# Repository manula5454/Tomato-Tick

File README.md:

# TomatoTick 2D Pomodoro Timer PCB only 
A PCB in the shape of a Tomato that runs a pomodoro timer of 30 minutes studying and 5 minutes break on repeat.
Here is the final render of my project!!

## This project is used to have a physical timer for studying that is a physical object instead of a digital site/app. The TomatoTick is meant to exist only as a PCB for a theatrical aspect and easy build process. The microchip is a XIAO RP2350 and powers the main display of an OLED SSD1306 which repeats a 30 minutes timer and 5 minute break when started. 

* Pomodoro Timer
* Quick and Easy digital timer build
* Exam study help

## Using this repo:
1. Code is located in [Arduino](Arduino)
2. Kicad files including libraries, schematics, pcb etc. are located in [PCB](PCB)
3. Gerbers.zip can be used to directly send PCB to vendors.

## heres how I made the project :)
1. Used Kicad and made a simple schematic with my parts (see BOM.csv)
2. Download all the Seeed libraries for the XIAO 2350
3. After the schematic is finished turn into PCB view and simply make a tomato shape on the edge faces layer
4. Add the traces to each component (use the render image above for reference)
5. Change the film colour to add the 'red' tomato

## Code - Arduino IDE
Libraries : 

#include <Wire.h>

#include <Adafruit_GFX.h>

#include <Adafruit_SSD1306.h>

(Can all be found inside the IDE library )

void(displayStudytime) -- Displays remaining study time on OLED screen
void(displayBreaktime) -- Displays remaining study time on OLED

buttonPin -- 1 press = pause, long press = reset {rp.2040 reboot();}

LED functions - builds up (e.g. LED5 lights up, then LED4....)

## Schematic of Tomato-Tick

### Bill of Materials (See BOM.cv)

| Reference | Part | Qty | Description | Vendor | Unit Price | Link |
| :--- | :--- | :---: | :--- | :--- | :---: | :--- |
| U2 | XIAO RP2350 | 1 | Microcontroller module | Seeed Studio | $5.90 | https://seeedstudio.com |
| D0 D1 D2 D3 D6 D7 | LED 3mm | 6 | Countdown LEDs | Core Electronics | $0.60 | https://core-electronics.com.au |
| R0 R1 R2 R3 R6 R7 | 330R resistor | 6 | LED current-limit resistors | Core Electronics | $1.58 | https://core-electronics.com.au |
| R9 | 1k resistor | 1 | Transistor base resistor | N/A | N/A | *Have one at home* |
| Q1 | 2N3904 transistor | 1 | NPN transistor for the buzzer | Core Electronics | $0.30 | https://core-electronics.com.au |
| SW2 | 6mm tactile button | 1 | Pause and reset button | Core Electronics | $0.36 | https://core-electronics.com.au |
| BZ1 | 5V active buzzer | 1 | Alert buzzer | Core Electronics | $0.27 | https://core-electronics.com.au |
| J1 | 1x4 pin header | 1 | OLED connector | Core Electronics | $0.11 | https://core-electronics.com.au |
| U1 | 1x7 pin header | 2 | Microcontroller connector | Core Electronics | $1.26 | https://core-electronics.com.au |
| OLED1 | White I2C OLED display (SSD1306) | 1 | 0.96in display | Core Electronics | $5.05 | https://core-electronics.com.au |
|     |  |                                  |  |               Shipping & GST Cost | $5.99 |  |
|     |  |                                  |  |               Total Cost | $25.63 |  |

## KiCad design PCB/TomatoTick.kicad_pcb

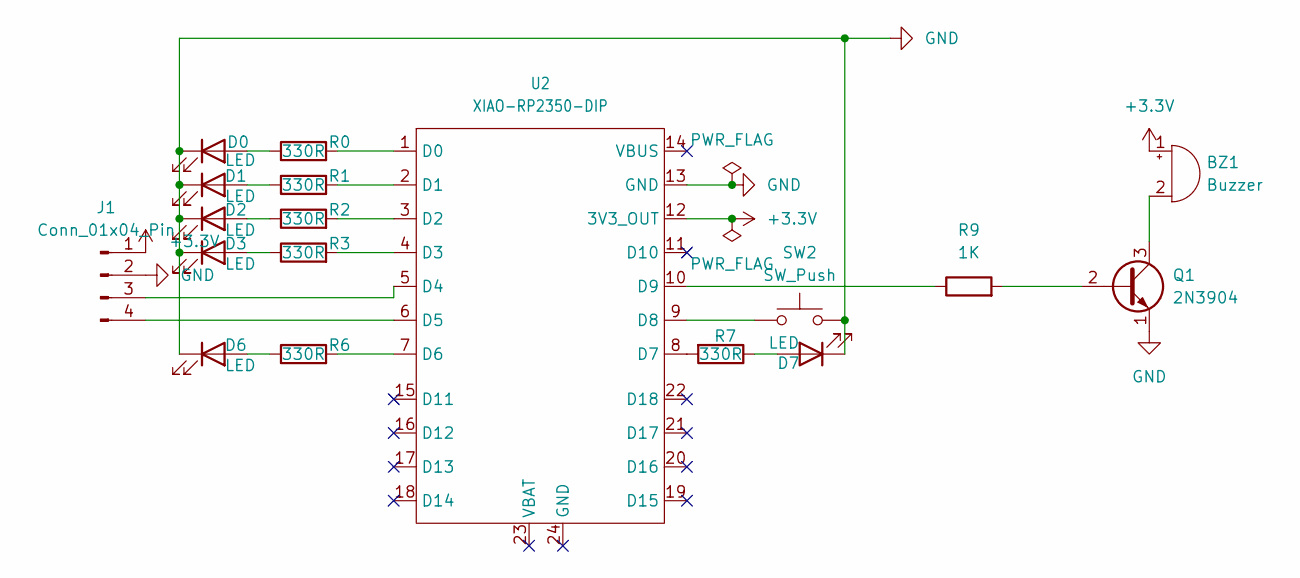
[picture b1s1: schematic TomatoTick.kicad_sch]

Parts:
BZ1: Buzzer; Buzzer_12x9.5RM7.6
D0, D1, D2, D3, D6, D7: LED; LED_D3.0mm
J1: Conn_01x04_Pin; PinSocket_1x04_P2.54mm_Vertical
Q1: 2N3904; TO-92_Inline
R0, R1, R2, R3, R6, R7: 330R; R_Axial_DIN0207_L6.3mm_D2.5mm_P7.62mm_Horizontal
R9: 1K; R_Axial_DIN0207_L6.3mm_D2.5mm_P7.62mm_Horizontal
SW2: SW_Push; SW_PUSH_6mm
U2: XIAO-RP2350-DIP

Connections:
+3.3V: BZ1.1 (+), J1.1, U2.12 (3V3_OUT)
GND: D0.1 (K), D1.1 (K), D2.1 (K), D3.1 (K), D6.1 (K), D7.1 (K), J1.2, Q1.1 (E), SW2.2, U2.13 (GND)
unnamed: BZ1.2 (-), Q1.3 (C)
unnamed: D0.2 (A), R0.1
unnamed: D1.2 (A), R1.1
unnamed: D2.2 (A), R2.1
unnamed: D3.2 (A), R3.1
unnamed: D6.2 (A), R6.1
unnamed: D7.2 (A), R7.1
unnamed: J1.3, U2.5 (D4)
unnamed: J1.4, U2.6 (D5)
unnamed: Q1.2 (B), R9.2
unnamed: R0.2, U2.1 (D0)
unnamed: R1.2, U2.2 (D1)
unnamed: R2.2, U2.3 (D2)
unnamed: R3.2, U2.4 (D3)
unnamed: R6.2, U2.7 (D6)
unnamed: R7.2, U2.8 (D7)
unnamed: SW2.1, U2.9 (D8)
unnamed: R9.1, U2.10 (D9)

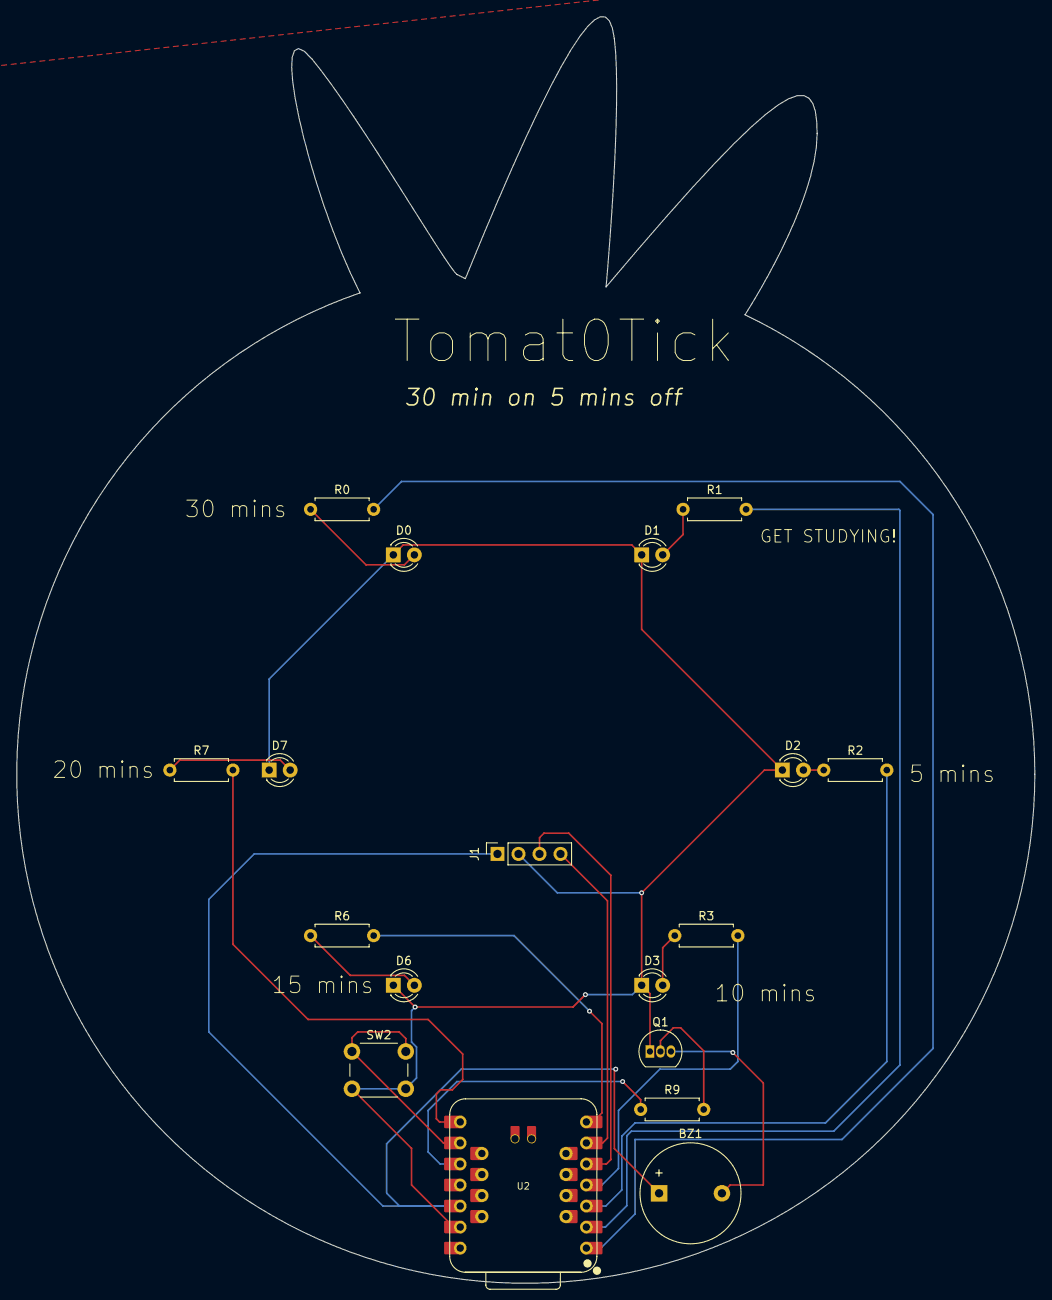
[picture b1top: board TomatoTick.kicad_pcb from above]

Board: 2 copper layers, 123.0 x 153.0 mm, 18 parts (0 on the bottom side), 20 nets.
